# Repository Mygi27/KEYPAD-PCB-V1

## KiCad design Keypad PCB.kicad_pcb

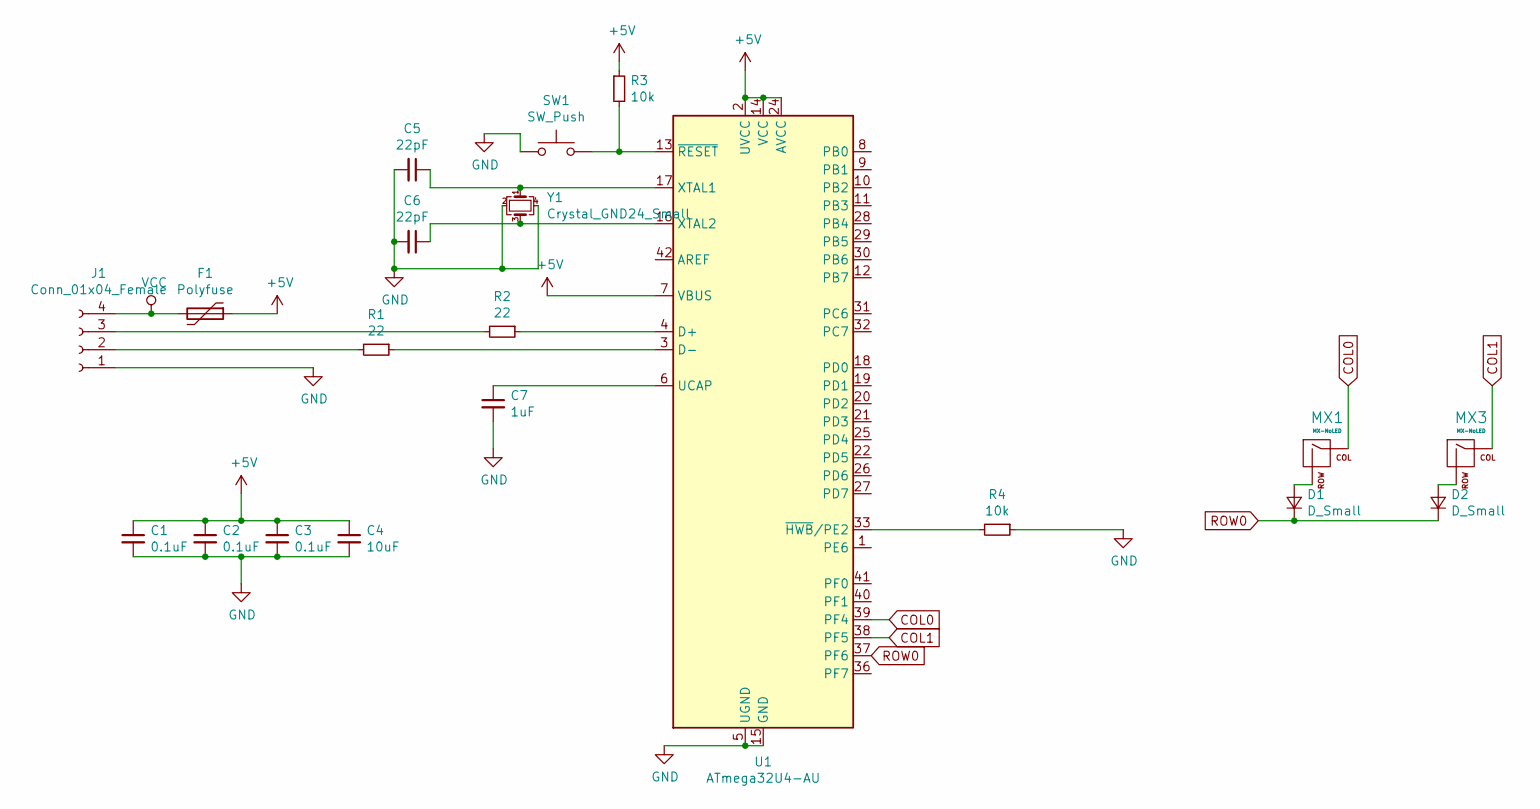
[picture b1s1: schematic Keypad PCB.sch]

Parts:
C1, C2, C3: 0.1uF; C_0805_2012Metric
C4: 10uF; C_0805_2012Metric
C5, C6: 22pF; C_0805_2012Metric
C7: 1uF; C_0805_2012Metric
D1, D2: D_Small; D_SOD-123
F1: Polyfuse; Fuse_1206_3216Metric
J1: Conn_01x04_Female; JST_SH_SM04B-SRSS-TB_04x1.00mm_Angled
MX1, MX3: MX-NoLED; MX-1U-NoLED
R1, R2: 22; R_0805_2012Metric
R3, R4: 10k; R_0805_2012Metric
SW1: SW_Push; SKQG-1155865
U1: ATmega32U4-AU; TQFP-44_10x10mm_P0.8mm
Y1: Crystal_GND24_Small; Crystal_SMD_3225-4Pin_3.2x2.5mm

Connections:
+5V: C1.1, C2.1, C3.1, C4.1, F1.1, R3.1, U1.2 (UVCC), U1.7 (VBUS), U1.14 (VCC), U1.24 (AVCC), U1.34 (VCC), U1.44 (AVCC)
COL0: MX1.1 (COL), U1.39 (PF4)
COL1: MX3.1 (COL), U1.38 (PF5)
GND: C1.2, C2.2, C3.2, C4.2, C5.2, C6.2, C7.2, J1.1, R4.1, SW1.1, U1.5 (UGND), U1.15 (GND), U1.23 (GND), U1.35 (GND), U1.43 (GND), Y1.2, Y1.4
unnamed: C5.1, U1.17 (XTAL1), Y1.1
unnamed: C6.1, U1.16 (XTAL2), Y1.3
unnamed: C7.1, U1.6 (UCAP)
unnamed: D1.2 (A), MX1.2 (ROW)
unnamed: D2.2 (A), MX3.2 (ROW)
unnamed: J1.2, R1.2
unnamed: J1.3, R2.2
unnamed: R1.1, U1.3 (D-)
unnamed: R2.1, U1.4 (D+)
unnamed: R3.2, SW1.2, U1.13 (~RESET)
unnamed: R4.2, U1.33 (~HWB~/PE2)
ROW0: D1.1 (K), D2.1 (K), U1.37 (PF6)
VCC: F1.2, J1.4

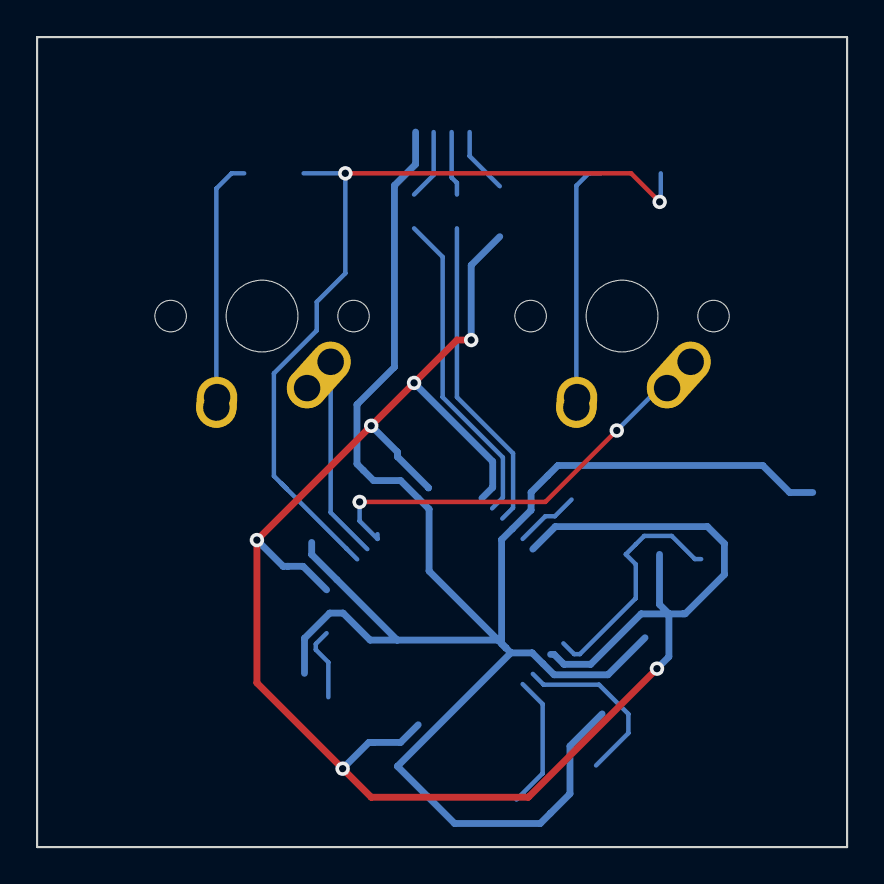
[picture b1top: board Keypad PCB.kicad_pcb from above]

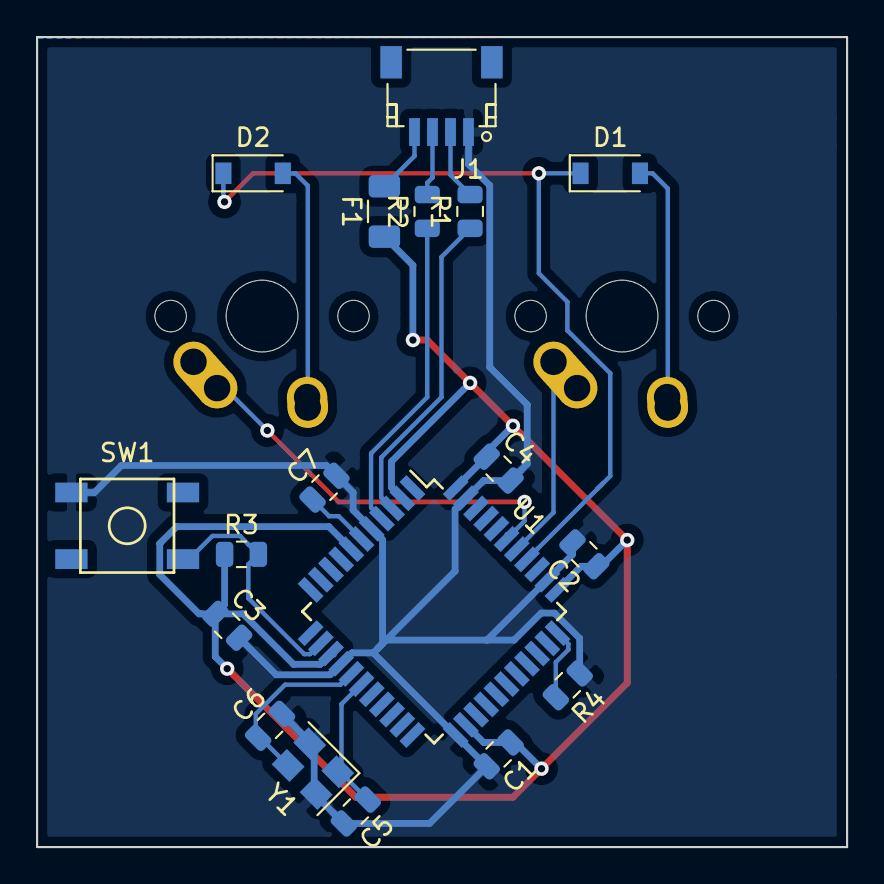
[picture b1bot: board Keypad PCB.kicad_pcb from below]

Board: 2 copper layers, 45.0 x 45.0 mm, 20 parts (18 on the bottom side), 17 nets.

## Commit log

2023-02-05 Création des fichier kicad
2023-02-05 Add submodules
2023-02-05 ajout des librairies
2023-02-05 Schematics
2023-02-05 PCB sans root
2023-02-05 Avancement sur le rooting du pcb
2023-02-06 avancement sur le pcb
2023-02-06 ça avance
2023-02-06 OMG ?
2023-02-06 Alors là
2023-02-06 jcrois c bon hein
2023-02-07 nettoyage
